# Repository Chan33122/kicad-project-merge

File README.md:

# kicad-project-merge

Merge two KiCad 8 projects into a single ready-to-open project — without
breaking the schematic↔PCB link.

## Motivation

PCB fabricators typically require a minimum panel size (e.g. 50×50 mm). When two small prototype boards are panelised together, standard KiCad merge methods re-annotate reference designators, breaking the match between the physical silkscreen, schematic, BOM, and test procedures. 

## The problem

KiCad links PCB footprints to schematic symbols via a UUID stored in the
footprint's `(path "/SYMBOL_UUID")` field. Copy-pasting symbols in the
editor reassigns new UUIDs, breaking every footprint↔symbol link silently.
KiCad then falls back to reference-string matching and re-associates
footprints incorrectly, corrupting the merged design.

## What this tool is for

The primary use case is **proto panelisation**: two small boards merged
onto one panel to meet a fabricator's minimum panel size requirement
(typically 50×50 mm).

The guarantee the tool provides is:

> Every reference designator on the physical silkscreen matches exactly
> what is in the merged schematic and BOM — with zero re-annotation.

This keeps test procedures, probe notes, and firmware pin maps consistent
from the moment the panel arrives on the bench.

## The solution

This tool merges entirely by **text concatenation**, preserving every UUID
byte-for-byte. Only three fields change:

| Field | Change |
|---|---|
| SCH `(project "old")` | → `(project "merge")` |
| SCH `(path "/old-sheet-uuid")` | → `(path "/new-uuid")` |
| PCB `(sheetfile "old.kicad_sch")` | → `(sheetfile "merge.kicad_sch")` |

## Usage

```bash
python3 merge_projects.py  Project1/  Project2/
```

Produces a single KiCad project folder beside the source projects:

- Merge-Project1-Project2/
- Merge-Project1-Project2.kicad_pro   ← open this in KiCad
- Merge-Project1-Project2.kicad_sch
- Merge-Project1-Project2.kicad_pcb
- Merge-Project1-Project2.kicad_prl

Dry-run first to verify everything before writing:

```bash
python3 merge_projects.py  Project1/  Project2/  --dry-run
```

Optional gap overrides:

```bash
python3 merge_projects.py  Project1/  Project2/  --gap-sch 80  --gap-pcb 40
```

## What the three stages do

**Stage 1 — Reference normalisation** (`kicad_ref_normalise.py`)
- Compacts project1 refs to a dense 1..N range per prefix (C, R, U …)
- Shifts project2 refs to start above project1's maxima
- Repairs any split-state files where `(property "Reference")` and
  `(instances/reference)` disagree — a common artifact of prior partial operations
- Verifies no overlap before writing

**Stage 2 — Schematic merge** (`kicad_sch_merge.py`)
- Finds Y_max of project1 schematic content
- Shifts all project2 coordinates down by Y_max + gap (default 50.8 mm)
- Merges `lib_symbols` blocks (union, deduplicated by name)
- Adds a labelled dashed box around each project zone
- Sets a custom `User W H` paper size fitted to the merged content

**Stage 3 — PCB merge** (`kicad_pcb_merge.py`)
- Places project2 board to the right of project1 (X shift)
- Footprint-internal coordinates (pad positions) are relative and are NOT shifted
- Merges net tables by name — shared nets (GND, +3V3) get one ID
- Adds labelled boxes on F.SilkS
- Sets a custom paper size fitted to both boards

## Requirements

- Python 3.10+
- KiCad 8 (S-expression format — likely compatible with KiCad 6/7)
- No external Python packages required

## Files

- merge_projects.py           ← single entry point
- kicad_ref_normalise.py      ← stage 1
- kicad_sch_merge.py          ← stage 2
- kicad_pcb_merge.py          ← stage 3

All four scripts must be in the same directory.

## ⚠ Read before opening the merged project in KiCad

### Net isolation — shared net names

Power nets and signal nets with identical names in both projects (e.g.
`GND`, `+3V3`, `+1V8`, `+5V`) are automatically renamed in the offset
project by adding a `__` prefix:

| Original (same-project) | Renamed (offset-project) |
|---|---|
| `GND` | `__GND` |
| `+3V3` | `__+3V3` |
| `+1V8` | `__+1V8` |
| `+5V` | `__+5V` |

This renaming is applied consistently in three places:

- **Schematic power symbols** — the `(property "Value")` of every
  `#PWR<n>` symbol whose net name is shared. This is the field KiCad
  uses to assign the net name to all pins connected to that power rail.
- **Schematic wire labels** — any `(label)`, `(global_label)`, or
  `(hierarchical_label)` carrying a shared net name.
- **PCB net table and pad references** — the net name string in the
  top-level net table and inside every pad's `(net ID "name")` field,
  as well as zone fill `(net_name "name")` references.

The result is that the two boards are **fully electrically independent**
in the merged KiCad project. `GND` and `__GND` are separate nets with
no connection between them. KiCad will not show any inter-board ratsnest
or unrouted connections.

### What this means on the bench

The physical boards share no copper — each board's ground plane is its
own island on the panel. If you need the two boards to share a common
ground during test, add a wire between their GND test points manually.
This is the correct approach for an RF front-end panel where ground
coupling between two sensitive circuits would be undesirable anyway.

**The merged project is not plug-and-play. The following are expected and require manual attention:**

### PCB
- **Boards need manual repositioning** — the tool places them side by side with
  a fixed gap. You still need to arrange them into your final panel
  layout, add board-edge cuts, V-score lines, and tooling strips manually.

### Schematic
- **The two designs are not electrically connected** — the merge is
  purely additive. No cross-wiring is created.

---

## License

MIT — free to use, modify, and distribute.
Developed by Chandresh Sharma with Claude (Anthropic).

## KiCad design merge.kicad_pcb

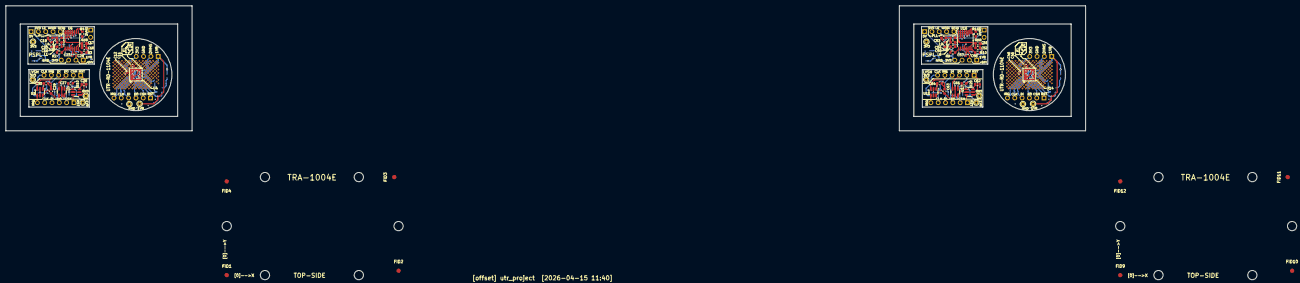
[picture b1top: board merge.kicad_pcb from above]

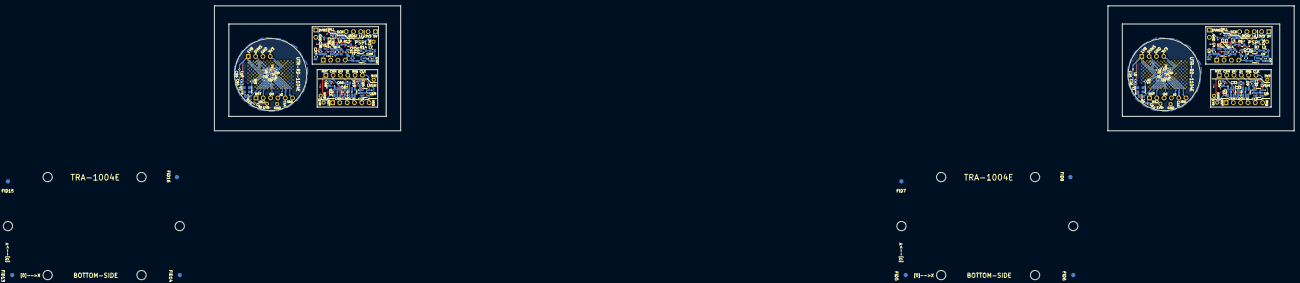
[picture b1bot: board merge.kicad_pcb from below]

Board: 4 copper layers, 374.5 x 43.3 mm, 548 parts (76 on the bottom side), 37 nets.

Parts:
C1, C3, C7, C35, C37, C41: 1u; C_0603_1608Metric
C2, C4, C6, C8, C17, C19, C27, C28, C29, C30, C31, C32, C33, C34, C36, C38, C40, C42, C51, C53, C61, C62, C63, C64, C65, C66, C67, C68: 100n; C_0603_1608Metric
C5, C39: 10u; C_0603_1608Metric
C9, C43: 470n; C_0402_1005Metric
C10, C11, C12, C14, C15, C26, C44, C45, C46, C48, C49, C60: 10u; C_0402_1005Metric
C13, C23, C24, C47, C57, C58: 100n; C_0402_1005Metric
C16, C18, C20, C50, C52, C54: 10p; C_0603_1608Metric
C21, C22, C55, C56: 1p; C_0402_1005Metric
C25, C59: 10n; C_0402_1005Metric
FID1, FID2, FID3, FID4, FID5, FID6, FID7, FID8, FID9, FID10, FID11, FID12, FID13, FID14, FID15, FID16: Fiducial; Fiducial_1.5mm_Mask4.5mm
H1, H2, H3, H4, H5, H6, H7, H8, H9, H10, H11, H12: MountingHole; MountingHole_3.2mm_M3
J1, J2, J8, J9: Conn_01x04_Pin; PinHeader_1x04_P2.54mm_Vertical
J3, J4, J6, J10, J11, J13: Conn_01x06_Pin; PinHeader_1x06_P2.54mm_Vertical
J5, J12: Conn_01x05_Pin; PinHeader_1x05_P2.54mm_Vertical
J7, J14: Conn_01x02_Pin; PinHeader_1x02_P2.54mm_Vertical
L1, L4, L6, L9: RFC; L_0603_1608Metric
L2, L3, L7, L8: 600E; L_0603_1608Metric
L5, L10: 600E; L_0402_1005Metric
R1, R8: 150E; R_0402_1005Metric
R2, R3, R4, R9, R10, R11: 10K; R_0603_1608Metric
R5, R12: 1K; R_0603_1608Metric
R6, R7, R13, R14: 0E; R_0603_1608Metric
TP1, TP2, TP3, TP4, TP5, TP6, TP197, TP198, TP199, TP200, TP201, TP202: TestPoint; TestPoint_THTPad_D1.5mm_Drill0.7mm
TP7, TP8, TP9, TP10, TP11, TP12, TP13, TP14, TP15, TP16, TP17, TP18, TP19, TP20, TP21, TP22, TP23, TP24, TP25, TP26, TP27, TP28, TP29, TP30, TP31, TP32, TP33, TP34, TP35, TP36, TP37, TP38, TP39, TP40, TP41, TP42, TP43, TP44, TP45, TP46, TP47, TP48, TP49, TP50, TP51, TP52, TP53, TP54, TP55, TP56, TP57, TP58, TP59, TP60, TP61, TP62, TP63, TP64, TP65, TP66, TP67, TP68, TP69, TP70, TP71, TP72, TP73, TP74, TP75, TP76, TP77, TP78, TP79, TP80, TP81, TP82, TP83, TP84, TP85, TP86, TP87, TP88, TP89, TP90, TP91, TP92, TP93, TP94, TP95, TP96, TP97, TP98, TP99, TP100, TP101, TP102, TP103, TP104, TP105, TP106, TP107, TP108, TP109, TP110, TP111, TP112, TP113, TP114, TP115, TP116, TP117, TP118, TP119, TP120, TP121, TP122, TP123, TP124, TP125, TP126, TP127, TP128, TP129, TP130, TP131, TP132, TP133, TP134, TP135, TP136, TP137, TP138, TP139, TP140, TP141, TP142, TP143, TP144, TP145, TP146, TP147, TP148, TP149, TP150, TP151, TP152, TP153, TP154, TP155, TP156, TP157, TP158, TP159, TP160, TP161, TP162, TP163, TP164, TP165, TP166, TP167, TP168, TP169, TP170, TP171, TP172, TP173, TP174, TP175, TP176, TP177, TP178, TP179, TP180, TP181, TP182, TP183, TP184, TP185, TP186, TP187, TP188, TP189, TP190, TP191, TP192, TP193, TP194, TP195, TP196, TP203, TP204, TP205, TP206, TP207, TP208, TP209, TP210, TP211, TP212, TP213, TP214, TP215, TP216, TP217, TP218, TP219, TP220, TP221, TP222, TP223, TP224, TP225, TP226, TP227, TP228, TP229, TP230, TP231, TP232, TP233, TP234, TP235, TP236, TP237, TP238, TP239, TP240, TP241, TP242, TP243, TP244, TP245, TP246, TP247, TP248, TP249, TP250, TP251, TP252, TP253, TP254, TP255, TP256, TP257, TP258, TP259, TP260, TP261, TP262, TP263, TP264, TP265, TP266, TP267, TP268, TP269, TP270, TP271, TP272, TP273, TP274, TP275, TP276, TP277, TP278, TP279, TP280, TP281, TP282, TP283, TP284, TP285, TP286, TP287, TP288, TP289, TP290, TP291, TP292, TP293, TP294, TP295, TP296, TP297, TP298, TP299, TP300, TP301, TP302, TP303, TP304, TP305, TP306, TP307, TP308, TP309, TP310, TP311, TP312, TP313, TP314, TP315, TP316, TP317, TP318, TP319, TP320, TP321, TP322, TP323, TP324, TP325, TP326, TP327, TP328, TP329, TP330, TP331, TP332, TP333, TP334, TP335, TP336, TP337, TP338, TP339, TP340, TP341, TP342, TP343, TP344, TP345, TP346, TP347, TP348, TP349, TP350, TP351, TP352, TP353, TP354, TP355, TP356, TP357, TP358, TP359, TP360, TP361, TP362, TP363, TP364, TP365, TP366, TP367, TP368, TP369, TP370, TP371, TP372, TP373, TP374, TP375, TP376, TP377, TP378, TP379, TP380, TP381, TP382, TP383, TP384, TP385, TP386, TP387, TP388, TP389, TP390, TP391, TP392: TestPoint; Via60GHz
U1, U3, U7, U8, U9, U10, U11, U13, U17, U18, U19, U20: SN74LVC1T45DBV; SOT-23-6
U2, U12: LDLN025M18R; SOT-23-5
U4, U14: BGT60UTR11AIP; BGA28N50P8X8_405X405X90-V
U5, U15: LDLN025M33R; SOT-23-5
U6, U16: ADF4113BRUZ; TSSOP-16_4.4x5mm_P0.65mm
Y1, Y2: KC2016 80MHz; Oscillator_SMD_Kyocera_KC2520Z-4Pin_2.5x2.0mm

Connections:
+1V8: C3.2, C4.2, C11.2, C12.2, C13.2, C14.2, C15.2, C21.2, C22.2, C27.2, C29.2, C31.2, C33.2, C37.2, C38.2, C45.2, C46.2, C47.2, C48.2, C49.2, C55.2, C56.2, C61.2, C63.2, C65.2, C67.2, J1.1, J2.1, J8.1, J9.1, L5.1, L10.1, R5.2, R12.2, TP1.1, TP2.1, TP197.1, TP198.1, U1.6 (VCCB), U2.5 (OUT), U3.1 (VCCA), U4.A6 (VDDRF), U4.C8 (VDDRF), U4.F1 (VDDIO), U4.F8 (VDDRF), U4.G1 (VDDAD), U4.G8 (VDDVCO), U4.H4 (VDDPLL), U4.H6 (VDDRF), U7.6 (VCCB), U8.1 (VCCA), U9.1 (VCCA), U10.1 (VCCA), U11.6 (VCCB), U12.5 (OUT), U13.1 (VCCA), U14.A6 (VDDRF), U14.C8 (VDDRF), U14.F1 (VDDIO), U14.F8 (VDDRF), U14.G1 (VDDAD), U14.G8 (VDDVCO), U14.H4 (VDDPLL), U14.H6 (VDDRF), U17.6 (VCCB), U18.1 (VCCA), U19.1 (VCCA), U20.1 (VCCA)
+3V3: C7.2, C8.2, C10.2, C28.2, C30.2, C32.2, C34.2, C41.2, C42.2, C44.2, C62.2, C64.2, C66.2, C68.2, J1.4, J2.4, J5.2, J8.4, J9.4, J12.2, L1.2, L4.2, L6.2, L9.2, R4.2, R11.2, TP5.1, TP6.1, TP201.1, TP202.1, U1.1 (VCCA), U3.6 (VCCB), U4.H3 (VDDLF), U5.5 (OUT), U7.1 (VCCA), U8.6 (VCCB), U9.6 (VCCB), U10.6 (VCCB), U11.1 (VCCA), U13.6 (VCCB), U14.H3 (VDDLF), U15.5 (OUT), U17.1 (VCCA), U18.6 (VCCB), U19.6 (VCCB), U20.6 (VCCB)
+5V: J5.1, J12.1, R6.2, R7.2, R13.2, R14.2
/CLK: J3.5, J4.5, J10.5, J11.5, U4.A2 (CLK), U8.3 (A), U14.A2 (CLK), U18.3 (A)
/CLK3: J6.6, J13.6, U8.4 (B), U18.4 (B)
/CSN: J3.2, J4.2, J10.2, J11.2, U3.3 (A), U4.D1 (CS_N), U13.3 (A), U14.D1 (CS_N)
/CSN3: J6.2, J13.2, U3.4 (B), U13.4 (B)
/DI: J3.4, J4.4, J10.4, J11.4, U4.B1 (DI), U9.3 (A), U14.B1 (DI), U19.3 (A)
/DI3: J6.4, J13.4, U9.4 (B), U19.4 (B)
/DIV: C24.2, C58.2, J1.2, J2.2, J8.2, J9.2, U4.H7 (DIV), U14.H7 (DIV)
/DIVN: C23.1, C57.1, U6.5 (RFINB), U16.5 (RFINB)
/DIVP: C24.1, C58.1, U6.6 (RFINA), U16.6 (RFINA)
/DIV_N: J7.1, J14.1, U6.14 (MUXOUT), U16.14 (MUXOUT)
/DO: J3.3, J4.3, J10.3, J11.3, U4.C1 (DO), U7.4 (B), U14.C1 (DO), U17.4 (B)
/DO3: J6.3, J13.3, U7.3 (A), U17.3 (A)
/IRQ: J3.6, J4.6, J10.6, J11.6, U1.4 (B), U4.A3 (IRQ), U11.4 (B), U14.A3 (IRQ)
/IRQ3: J6.5, J13.5, U1.3 (A), U11.3 (A)
/PLL_LE: J5.3, J12.3, U6.13 (LE), U16.13 (LE)
/PLL_MOSI: J5.4, J12.4, U6.12 (DATA), U16.12 (DATA)
/PLL_SCK: J5.5, J12.5, U6.11 (CLK), U16.11 (CLK)
/RST: J3.1, J4.1, J10.1, J11.1, U4.E1 (RST), U10.3 (A), U14.E1 (RST), U20.3 (A)
/RST3: J6.1, J13.1, U10.4 (B), U20.4 (B)
GND: C1.1, C2.1, C3.1, C4.1, C5.1, C6.1, C7.1, C8.1, C9.1, C10.1, C11.1, C12.1, C13.1, C14.1, C15.1, C16.1, C17.1, C18.1, C19.1, C20.1, C21.1, C22.1, C23.2, C25.2, C26.2, C27.1, C28.1, C29.1, C30.1, C31.1, C32.1, C33.1, C34.1, C35.1, C36.1, C37.1, C38.1, C39.1, C40.1, C41.1, C42.1, C43.1, C44.1, C45.1, C46.1, C47.1, C48.1, C49.1, C50.1, C51.1, C52.1, C53.1, C54.1, C55.1, C56.1, C57.2, C59.2, C60.2, C61.1, C62.1, C63.1, C64.1, C65.1, C66.1, C67.1, C68.1, J1.3, J2.3, J7.2, J8.3, J9.3, J14.2, R2.1, R3.2, R9.1, R10.2, TP3.1, TP4.1, TP7.1, TP8.1, TP9.1, TP10.1, TP11.1, TP12.1, TP13.1, TP14.1, TP15.1, TP16.1, TP17.1, TP18.1, TP19.1, TP20.1, TP21.1, TP22.1, TP23.1, TP24.1, TP25.1, TP26.1, TP27.1, TP28.1, TP29.1, TP30.1, TP31.1, TP32.1, TP33.1, TP34.1, TP35.1, TP36.1, TP37.1, TP38.1, TP39.1, TP40.1, TP41.1, TP42.1, TP43.1, TP44.1, TP45.1, TP46.1, TP47.1, TP48.1, TP49.1, TP50.1, TP51.1, TP52.1, TP53.1, TP54.1, TP55.1, TP56.1, TP57.1, TP58.1, TP59.1, TP60.1, TP61.1, TP62.1, TP63.1, TP64.1, TP65.1, TP66.1, TP67.1, TP68.1, TP69.1, TP70.1, TP71.1, TP72.1, TP73.1, TP74.1, TP75.1, TP76.1, TP77.1, TP78.1, TP79.1, TP80.1, TP81.1, TP82.1, TP83.1, TP84.1, TP85.1, TP86.1, TP87.1, TP88.1, TP89.1, TP90.1, TP91.1, TP92.1, TP93.1, TP94.1, TP95.1, TP96.1, TP97.1, TP98.1, TP99.1, TP100.1, TP101.1, TP102.1, TP103.1, TP104.1, TP105.1, TP106.1, TP107.1, TP108.1, TP109.1, TP110.1, TP111.1, TP112.1, TP113.1, TP114.1, TP115.1, TP116.1, TP117.1, TP118.1, TP119.1, TP120.1, TP121.1, TP122.1, TP123.1, TP124.1, TP125.1, TP126.1, TP127.1, TP128.1, TP129.1, TP130.1, TP131.1, TP132.1, TP133.1, TP134.1, TP135.1, TP136.1, TP137.1, TP138.1, TP139.1, TP140.1, TP141.1, TP142.1, TP143.1, TP144.1, TP145.1, TP146.1, TP147.1, TP148.1, TP149.1, TP150.1, TP151.1, TP152.1, TP153.1, TP154.1, TP155.1, TP156.1, TP157.1, TP158.1, TP159.1, TP160.1, TP161.1, TP162.1, TP163.1, TP164.1, TP165.1, TP166.1, TP167.1, TP168.1, TP169.1, TP170.1, TP171.1, TP172.1, TP173.1, TP174.1, TP175.1, TP176.1, TP177.1, TP178.1, TP179.1, TP180.1, TP181.1, TP182.1, TP183.1, TP184.1, TP185.1, TP186.1, TP187.1, TP188.1, TP189.1, TP190.1, TP191.1, TP192.1, TP193.1, TP194.1, TP195.1, TP196.1, TP199.1, TP200.1, TP203.1, TP204.1, TP205.1, TP206.1, TP207.1, TP208.1, TP209.1, TP210.1, TP211.1, TP212.1, TP213.1, TP214.1, TP215.1, TP216.1, TP217.1, TP218.1, TP219.1, TP220.1, TP221.1, TP222.1, TP223.1, TP224.1, TP225.1, TP226.1, TP227.1, TP228.1, TP229.1, TP230.1, TP231.1, TP232.1, TP233.1, TP234.1, TP235.1, TP236.1, TP237.1, TP238.1, TP239.1, TP240.1, TP241.1, TP242.1, TP243.1, TP244.1, TP245.1, TP246.1, TP247.1, TP248.1, TP249.1, TP250.1, TP251.1, TP252.1, TP253.1, TP254.1, TP255.1, TP256.1, TP257.1, TP258.1, TP259.1, TP260.1, TP261.1, TP262.1, TP263.1, TP264.1, TP265.1, TP266.1, TP267.1, TP268.1, TP269.1, TP270.1, TP271.1, TP272.1, TP273.1, TP274.1, TP275.1, TP276.1, TP277.1, TP278.1, TP279.1, TP280.1, TP281.1, TP282.1, TP283.1, TP284.1, TP285.1, TP286.1, TP287.1, TP288.1, TP289.1, TP290.1, TP291.1, TP292.1, TP293.1, TP294.1, TP295.1, TP296.1, TP297.1, TP298.1, TP299.1, TP300.1, TP301.1, TP302.1, TP303.1, TP304.1, TP305.1, TP306.1, TP307.1, TP308.1, TP309.1, TP310.1, TP311.1, TP312.1, TP313.1, TP314.1, TP315.1, TP316.1, TP317.1, TP318.1, TP319.1, TP320.1, TP321.1, TP322.1, TP323.1, TP324.1, TP325.1, TP326.1, TP327.1, TP328.1, TP329.1, TP330.1, TP331.1, TP332.1, TP333.1, TP334.1, TP335.1, TP336.1, TP337.1, TP338.1, TP339.1, TP340.1, TP341.1, TP342.1, TP343.1, TP344.1, TP345.1, TP346.1, TP347.1, TP348.1, TP349.1, TP350.1, TP351.1, TP352.1, TP353.1, TP354.1, TP355.1, TP356.1, TP357.1, TP358.1, TP359.1, TP360.1, TP361.1, TP362.1, TP363.1, TP364.1, TP365.1, TP366.1, TP367.1, TP368.1, TP369.1, TP370.1, TP371.1, TP372.1, TP373.1, TP374.1, TP375.1, TP376.1, TP377.1, TP378.1, TP379.1, TP380.1, TP381.1, TP382.1, TP383.1, TP384.1, TP385.1, TP386.1, TP387.1, TP388.1, TP389.1, TP390.1, TP391.1, TP392.1, U1.2 (GND), U1.5 (DIR), U2.2 (GND), U3.2 (GND), U3.5 (DIR), U4.A1 (VSS), U4.A4 (VSS), U4.A5 (VSS), U4.A7 (VSS), U4.A8 (VSS), U4.B8 (VSS), U4.D8 (VSS), U4.E8 (VSS), U4.H1 (VSS), U4.H8 (VSS), U5.2 (GND), U6.3 (CPGND), U6.4 (AGND), U6.9 (DGND), U7.2 (GND), U7.5 (DIR), U8.2 (GND), U8.5 (DIR), U9.2 (GND), U9.5 (DIR), U10.2 (GND), U10.5 (DIR), U11.2 (GND), U11.5 (DIR), U12.2 (GND), U13.2 (GND), U13.5 (DIR), U14.A1 (VSS), U14.A4 (VSS), U14.A5 (VSS), U14.A7 (VSS), U14.A8 (VSS), U14.B8 (VSS), U14.D8 (VSS), U14.E8 (VSS), U14.H1 (VSS), U14.H8 (VSS), U15.2 (GND), U16.3 (CPGND), U16.4 (AGND), U16.9 (DGND), U17.2 (GND), U17.5 (DIR), U18.2 (GND), U18.5 (DIR), U19.2 (GND), U19.5 (DIR), U20.2 (GND), U20.5 (DIR), Y1.2 (GND), Y2.2 (GND)
unnamed: L2.1, L7.1, R7.1, R14.1
unnamed: L3.1, L8.1, R6.1, R13.1
unnamed: C1.2, C2.2, C35.2, C36.2, L3.2, L8.2, U2.1 (IN), U2.3 (EN), U12.1 (IN), U12.3 (EN)
unnamed: R1.1, R8.1, U4.H5 (OSC_CLK), U14.H5 (OSC_CLK)
unnamed: C9.2, C43.2, U4.H2 (VAREF), U14.H2 (VAREF)
unnamed: C5.2, C6.2, C39.2, C40.2, L2.2, L7.2, U5.1 (IN), U5.3 (EN), U15.1 (IN), U15.3 (EN)
unnamed: C16.2, C17.2, C18.2, C50.2, C51.2, C52.2, L1.1, L6.1, U6.7 (AVDD), U6.16 (VP), U16.7 (AVDD), U16.16 (VP)
unnamed: R4.1, R11.1, U6.10 (CE), U16.10 (CE)
unnamed: C19.2, C20.2, C53.2, C54.2, L4.1, L9.1, U6.15 (DVDD), U16.15 (DVDD)
unnamed: R3.1, R10.1, U6.8 (REFIN), U16.8 (REFIN)
unnamed: R2.2, R9.2, U6.1 (RSET), U16.1 (RSET)
unnamed: R1.2, R8.2, Y1.3 (CLK), Y2.3 (CLK)
unnamed: R5.1, R12.1, Y1.1 (INH), Y2.1 (INH)
unnamed: C25.1, C26.1, C59.1, C60.1, L5.2, L10.2, Y1.4 (VCC), Y2.4 (VCC)
